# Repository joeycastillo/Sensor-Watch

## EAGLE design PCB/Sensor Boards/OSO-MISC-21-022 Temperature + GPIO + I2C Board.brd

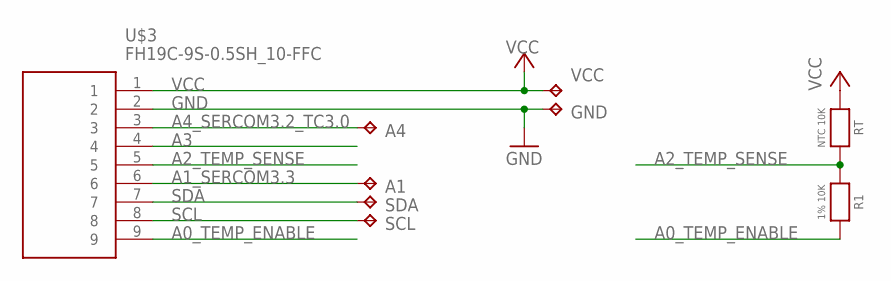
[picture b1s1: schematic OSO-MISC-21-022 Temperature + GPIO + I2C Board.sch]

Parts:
A1, A4: TPB1,27; B1,27
GND: TPB1,27; B1,27
R1: 1% 10K; _0603MP
RT: NTC 10K; _0603MP
SCL: TPB1,27; B1,27
SDA: TPB1,27; B1,27
U$3: FH19C-9S-0.5SH_10-FFC; FH19C9S05SH10-FFC
VCC: TPB1,27; B1,27

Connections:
A0_TEMP_ENABLE: R1.2, U$3.9
A1_SERCOM3.3: A1.TP, U$3.6
A2_TEMP_SENSE: R1.1, RT.2, U$3.5
A3: U$3.4
A4_SERCOM3.2_TC3.0: A4.TP, U$3.3
GND: GND.TP, U$3.2
SCL: SCL.TP, U$3.8
SDA: SDA.TP, U$3.7
VCC: RT.1, U$3.1, VCC.TP

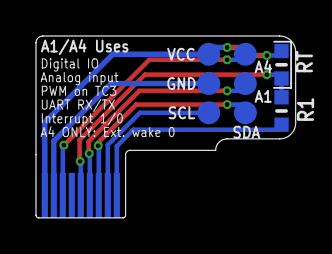
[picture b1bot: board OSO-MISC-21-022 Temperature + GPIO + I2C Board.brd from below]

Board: 2 copper layers, 14.4 x 10.1 mm, 9 parts (8 on the bottom side), 8 nets.

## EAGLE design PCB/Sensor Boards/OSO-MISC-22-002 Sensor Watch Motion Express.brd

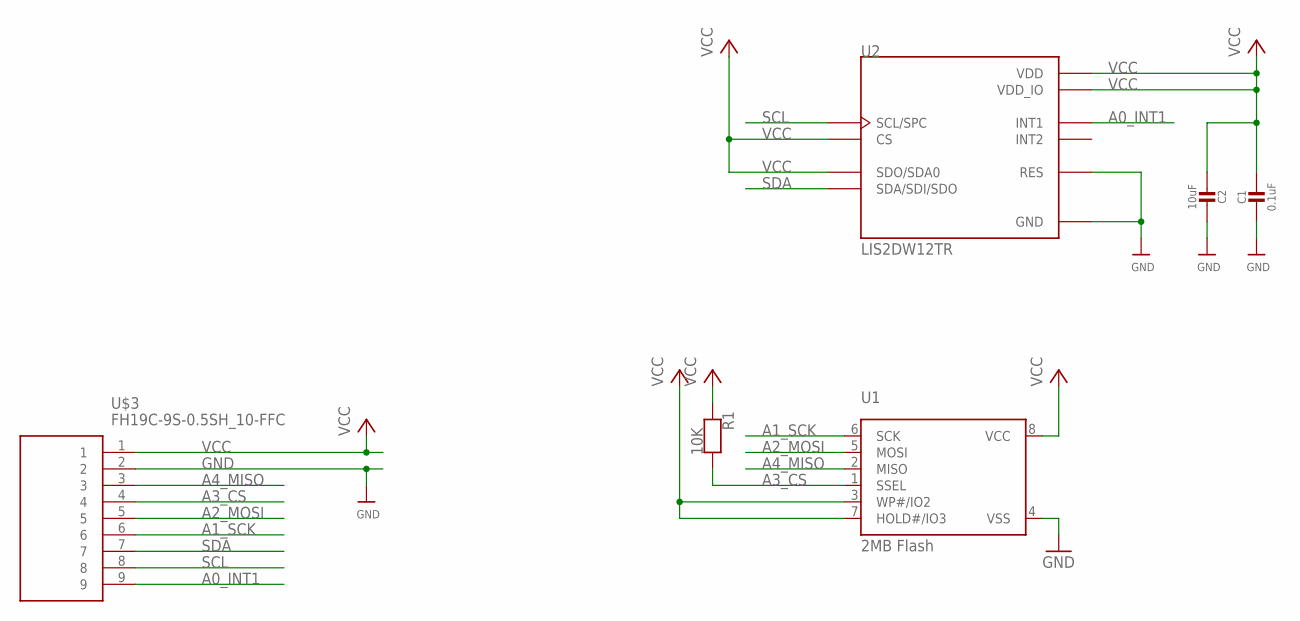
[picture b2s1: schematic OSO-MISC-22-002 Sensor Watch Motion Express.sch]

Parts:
C1: 0.1uF; _0603MP
C2: 10uF; _0603MP
R1: 10K; _0603MP
U1: 2MB Flash; USON8
U2: LIS2DW12TR; LGA12R50P4X4_200X200X70
U$3: FH19C-9S-0.5SH_10-FFC; FH19C9S05SH10-FFC

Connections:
A0_INT1: U2.12 (INT1), U$3.9
A1_SCK: U1.6 (SCK), U$3.6
A2_MOSI: U1.5 (MOSI), U$3.5
A3_CS: R1.2, U1.1 (SSEL), U$3.4
A4_MISO: U1.2 (MISO), U$3.3
GND: C1.2, C2.1, U1.4 (VSS), U2.6 (GND), U2.7 (RES), U2.8 (GND), U$3.2
SCL: U2.1 (SCL/SPC), U$3.8
SDA: U2.4 (SDA/SDI/SDO), U$3.7
VCC: C1.1, C2.2, R1.1, U1.3 (WP#/IO2), U1.7 (HOLD#/IO3), U1.8 (VCC), U2.2 (CS), U2.3 (SDO/SDA0), U2.9 (VDD), U2.10 (VDD_IO), U$3.1

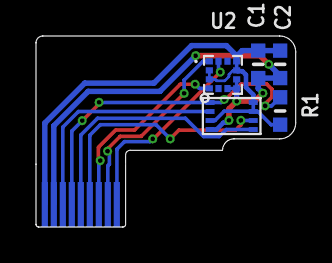
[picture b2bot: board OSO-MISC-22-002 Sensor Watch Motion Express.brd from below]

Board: 2 copper layers, 14.4 x 10.6 mm, 6 parts (5 on the bottom side), 9 nets.

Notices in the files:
parts and their libraries:
My Stuff: cc-by-sa 4.0
microbuilder: This work is placed in the public domain, and may be freely used for commercial and non-commercial work with the following conditions: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
